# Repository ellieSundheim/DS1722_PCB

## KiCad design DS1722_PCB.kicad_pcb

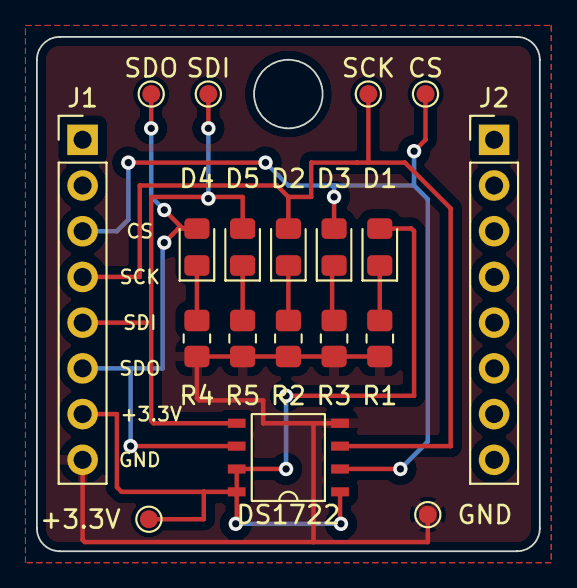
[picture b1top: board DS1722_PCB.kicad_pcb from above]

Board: 2 copper layers, 27.9 x 28.6 mm, 19 parts (0 on the bottom side), 11 nets.

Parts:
+3.3V: TestPoint_Pad_D1.0mm
CS: TestPoint_Pad_D1.0mm
D1, D2, D3, D4, D5: LED; LED_0805_2012Metric_Pad1.15x1.40mm_HandSolder
GND: TestPoint_Pad_D1.0mm
J1, J2: Conn_01x08_Male; PinHeader_1x08_P2.54mm_Vertical
R1, R2, R3, R4, R5: 1k; R_0805_2012Metric_Pad1.20x1.40mm_HandSolder
SCK: TestPoint_Pad_D1.0mm
SDI: TestPoint_Pad_D1.0mm
SDO: TestPoint_Pad_D1.0mm
U1: DS1722; SOIC8-DS1722

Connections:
/+3.3V: +3.3V.1, D1.2 (A), J1.7, U1.1 (V_{DDD}), U1.7 (SERMODE), U1.8 (V_{DDA})
/CS: CS.1, D3.2 (A), J1.3, U1.2 (CE)
/MISO: D5.2 (A), J1.5, SDI.1, U1.5 (SDO)
/MOSI: D4.2 (A), J1.6, SDO.1, U1.6 (SDI)
/SCK: D2.2 (A), J1.4, SCK.1, U1.3 (SCLK)
GND: GND.1, J1.8, R1.2, R2.2, R3.2, R4.2, R5.2, U1.4 (GND)
unnamed: D1.1 (K), R1.1
unnamed: D2.1 (K), R2.1
unnamed: D3.1 (K), R3.1
unnamed: D4.1 (K), R4.1
unnamed: D5.1 (K), R5.1

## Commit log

2024-10-01 add gitignore
2024-10-01 Initial commit of schematic
2024-10-03 Footprints and starting layout
2024-10-04 Finished layout
2024-10-04 Gerbers
